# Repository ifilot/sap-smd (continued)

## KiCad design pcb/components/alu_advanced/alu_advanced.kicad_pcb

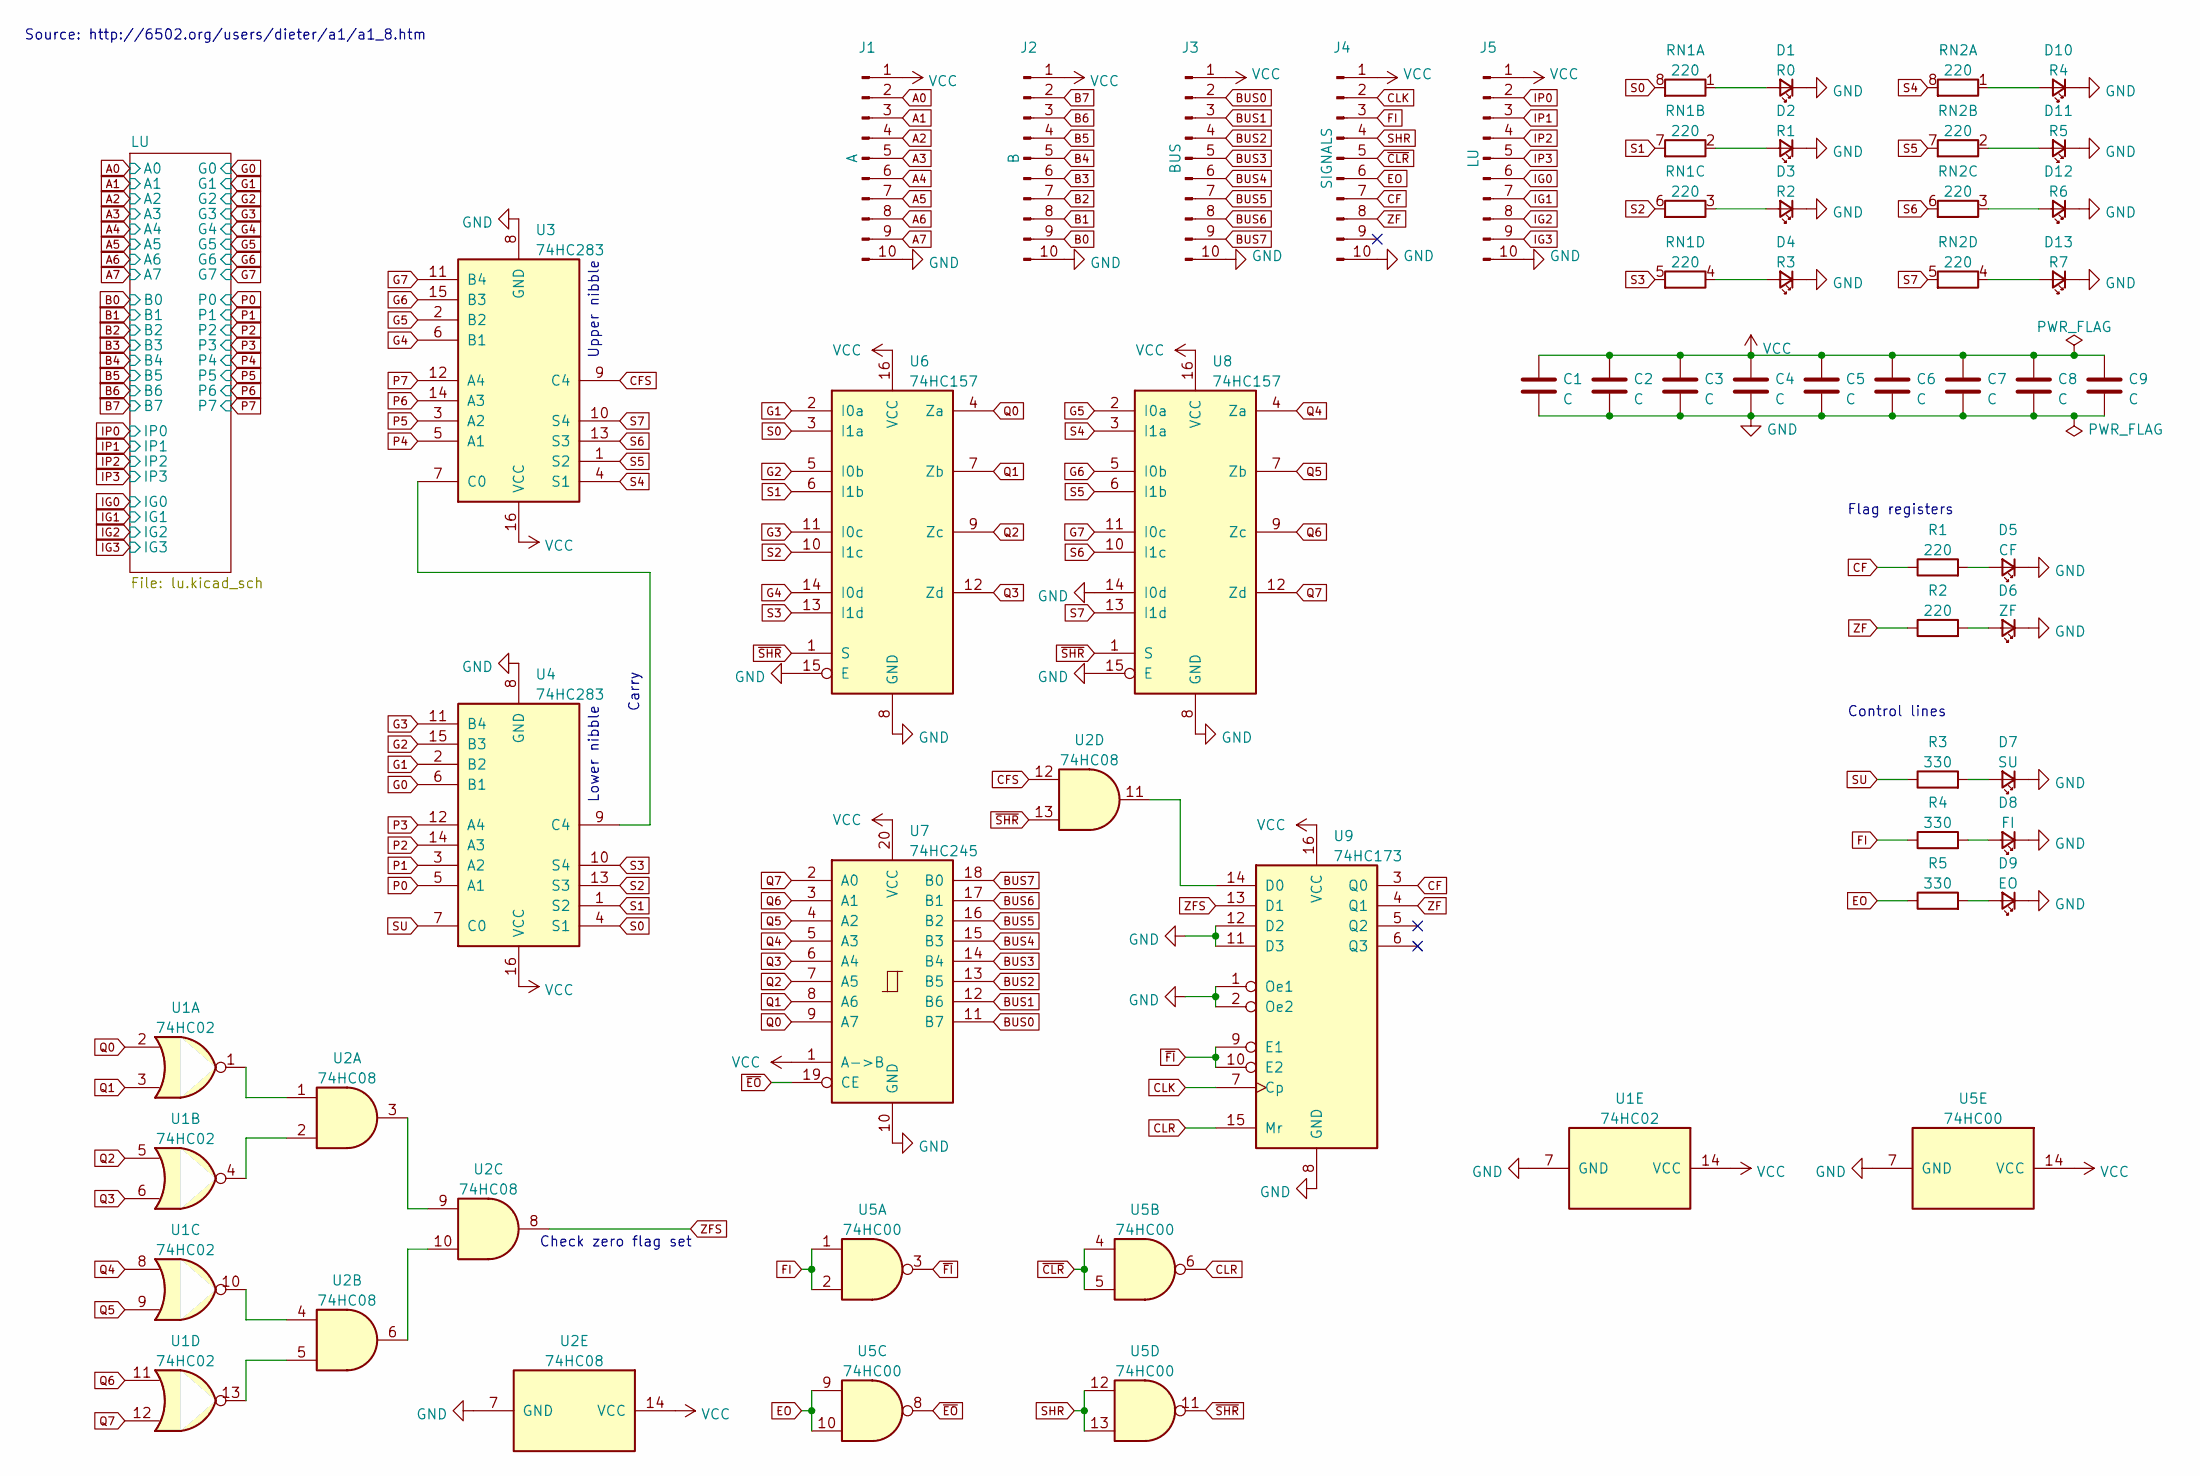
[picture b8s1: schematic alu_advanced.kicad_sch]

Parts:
C1, C2, C3, C4, C5, C6, C7, C8, C9: C; C_0805_2012Metric
D1: R0; LED_0805_2012Metric
D2: R1; LED_0805_2012Metric
D3: R2; LED_0805_2012Metric
D4: R3; LED_0805_2012Metric
D5: CF; LED_0805_2012Metric
D6: ZF; LED_0805_2012Metric
D7: SU; LED_0805_2012Metric
D8: FI; LED_0805_2012Metric
D9: EO; LED_0805_2012Metric
D10: R4; LED_0805_2012Metric
D11: R5; LED_0805_2012Metric
D12: R6; LED_0805_2012Metric
D13: R7; LED_0805_2012Metric
J1: A; PinHeader_1x10_P2.54mm_Vertical
J2: B; PinHeader_1x10_P2.54mm_Vertical
J3: BUS; PinHeader_1x10_P2.54mm_Vertical
J4: SIGNALS; PinHeader_1x10_P2.54mm_Vertical
J5: LU; PinHeader_1x10_P2.54mm_Vertical
R1, R2: 220; R_0805_2012Metric
R3, R4, R5: 330; R_0805_2012Metric
RN1, RN2: 220; R_Array_Convex_4x0603
U1: 74HC02; SO-14_3.9x8.65mm_P1.27mm
U2: 74HC08; SO-14_3.9x8.65mm_P1.27mm
U3, U4: 74HC283; SO-16_3.9x9.9mm_P1.27mm
U5: 74HC00; SO-14_3.9x8.65mm_P1.27mm
U6, U8: 74HC157; SO-16_3.9x9.9mm_P1.27mm
U7: 74HC245; SO-20_12.8x7.5mm_P1.27mm
U9: 74HC173; SO-16_3.9x9.9mm_P1.27mm

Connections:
A0: J1.2; also elsewhere on the board
A1: J1.3; also elsewhere on the board
A2: J1.4; also elsewhere on the board
A3: J1.5; also elsewhere on the board
A4: J1.6; also elsewhere on the board
A5: J1.7; also elsewhere on the board
A6: J1.8; also elsewhere on the board
A7: J1.9; also elsewhere on the board
B0: J2.9; also elsewhere on the board
B1: J2.8; also elsewhere on the board
B2: J2.7; also elsewhere on the board
B3: J2.6; also elsewhere on the board
B4: J2.5; also elsewhere on the board
B5: J2.4; also elsewhere on the board
B6: J2.3; also elsewhere on the board
B7: J2.2; also elsewhere on the board
BUS0: J3.2, U7.11 (B7)
BUS1: J3.3, U7.12 (B6)
BUS2: J3.4, U7.13 (B5)
BUS3: J3.5, U7.14 (B4)
BUS4: J3.6, U7.15 (B3)
BUS5: J3.7, U7.16 (B2)
BUS6: J3.8, U7.17 (B1)
BUS7: J3.9, U7.18 (B0)
CF: J4.7, R1.1, U9.3 (Q0)
CFS: U2.12, U3.9 (C4)
CLK: J4.2, U9.7 (Cp)
CLR: U5.6, U9.15 (Mr)
EO: J4.6, R5.1, U5.9, U5.10
FI: J4.3, R4.1, U5.1, U5.2
G0: U4.6 (B1); also elsewhere on the board
G1: U4.2 (B2), U6.2 (I0a); also elsewhere on the board
G2: U4.15 (B3), U6.5 (I0b); also elsewhere on the board
G3: U4.11 (B4), U6.11 (I0c); also elsewhere on the board
G4: U3.6 (B1), U6.14 (I0d); also elsewhere on the board
G5: U3.2 (B2), U8.2 (I0a); also elsewhere on the board
G6: U3.15 (B3), U8.5 (I0b); also elsewhere on the board
G7: U3.11 (B4), U8.11 (I0c); also elsewhere on the board
GND: C1.2, C2.2, C3.2, C4.2, C5.2, C6.2, C7.2, C8.2, C9.2, D1.1 (K), D2.1 (K), D3.1 (K), D4.1 (K), D5.1 (K), D6.1 (K), D7.1 (K), D8.1 (K), D9.1 (K), D10.1 (K), D11.1 (K), D12.1 (K), D13.1 (K), J1.10, J2.10, J3.10, J4.10, J5.10, U1.7 (GND), U2.7 (GND), U3.8 (GND), U4.8 (GND), U5.7 (GND), U6.8 (GND), U6.15 (E), U7.10 (GND), U8.8 (GND), U8.14 (I0d), U8.15 (E), U9.1 (Oe1), U9.2 (Oe2), U9.8 (GND), U9.11 (D3), U9.12 (D2); also elsewhere on the board
IG0: J5.6; also elsewhere on the board
IG1: J5.7; also elsewhere on the board
IG2: J5.8; also elsewhere on the board
IG3: J5.9; also elsewhere on the board
IP0: J5.2; also elsewhere on the board
IP1: J5.3; also elsewhere on the board
IP2: J5.4; also elsewhere on the board
IP3: J5.5; also elsewhere on the board
unnamed: D1.2 (A), RN1.1 (R1.1)
unnamed: D2.2 (A), RN1.2 (R2.1)
unnamed: D3.2 (A), RN1.3 (R3.1)
unnamed: D4.2 (A), RN1.4 (R4.1)
unnamed: D5.2 (A), R1.2
unnamed: D6.2 (A), R2.2
unnamed: D7.2 (A), R3.2
unnamed: D8.2 (A), R4.2
unnamed: D9.2 (A), R5.2
unnamed: D10.2 (A), RN2.1 (R1.1)
unnamed: D11.2 (A), RN2.2 (R2.1)
unnamed: D12.2 (A), RN2.3 (R3.1)
unnamed: D13.2 (A), RN2.4 (R4.1)
unnamed: U1.1, U2.1
unnamed: U1.4, U2.2
unnamed: U1.10, U2.4
unnamed: U1.13, U2.5
unnamed: U2.3, U2.9
unnamed: U2.6, U2.10
unnamed: U2.11, U9.14 (D0)
unnamed: U3.7 (C0), U4.9 (C4)
P0: U4.5 (A1); also elsewhere on the board
P1: U4.3 (A2); also elsewhere on the board
P2: U4.14 (A3); also elsewhere on the board
P3: U4.12 (A4); also elsewhere on the board
P4: U3.5 (A1); also elsewhere on the board
P5: U3.3 (A2); also elsewhere on the board
P6: U3.14 (A3); also elsewhere on the board
P7: U3.12 (A4); also elsewhere on the board
Q0: U1.2, U6.4 (Za), U7.9 (A7)
Q1: U1.3, U6.7 (Zb), U7.8 (A6)
Q2: U1.5, U6.9 (Zc), U7.7 (A5)
Q3: U1.6, U6.12 (Zd), U7.6 (A4)
Q4: U1.8, U7.5 (A3), U8.4 (Za)
Q5: U1.9, U7.4 (A2), U8.7 (Zb)
Q6: U1.11, U7.3 (A1), U8.9 (Zc)
Q7: U1.12, U7.2 (A0), U8.12 (Zd)
S0: RN1.8 (R1.2), U4.4 (S1), U6.3 (I1a)
S1: RN1.7 (R2.2), U4.1 (S2), U6.6 (I1b)
S2: RN1.6 (R3.2), U4.13 (S3), U6.10 (I1c)
S3: RN1.5 (R4.2), U4.10 (S4), U6.13 (I1d)
S4: RN2.8 (R1.2), U3.4 (S1), U8.3 (I1a)
S5: RN2.7 (R2.2), U3.1 (S2), U8.6 (I1b)
S6: RN2.6 (R3.2), U3.13 (S3), U8.10 (I1c)
S7: RN2.5 (R4.2), U3.10 (S4), U8.13 (I1d)
SHR: J4.4, U5.12, U5.13
SU: R3.1, U4.7 (C0)
VCC: C1.1, C2.1, C3.1, C4.1, C5.1, C6.1, C7.1, C8.1, C9.1, J1.1, J2.1, J3.1, J4.1, J5.1, U1.14 (VCC), U2.14 (VCC), U3.16 (VCC), U4.16 (VCC), U5.14 (VCC), U6.16 (VCC), U7.1 (A->B), U7.20 (VCC), U8.16 (VCC), U9.16 (VCC); also elsewhere on the board
ZF: J4.8, R2.1, U9.4 (Q1)
ZFS: U2.8, U9.13 (D1)
~CLR: J4.5, U5.4, U5.5
~EO: U5.8, U7.19 (CE)
~FI: U5.3, U9.9 (E1), U9.10 (E2)
~SHR: U2.13, U5.11, U6.1 (S), U8.1 (S)

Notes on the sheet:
Control lines
Flag registers
Upper nibble
Check zero flag set
Source: http://6502.org/users/dieter/a1/a1_8.htm
Carry
Lower nibble

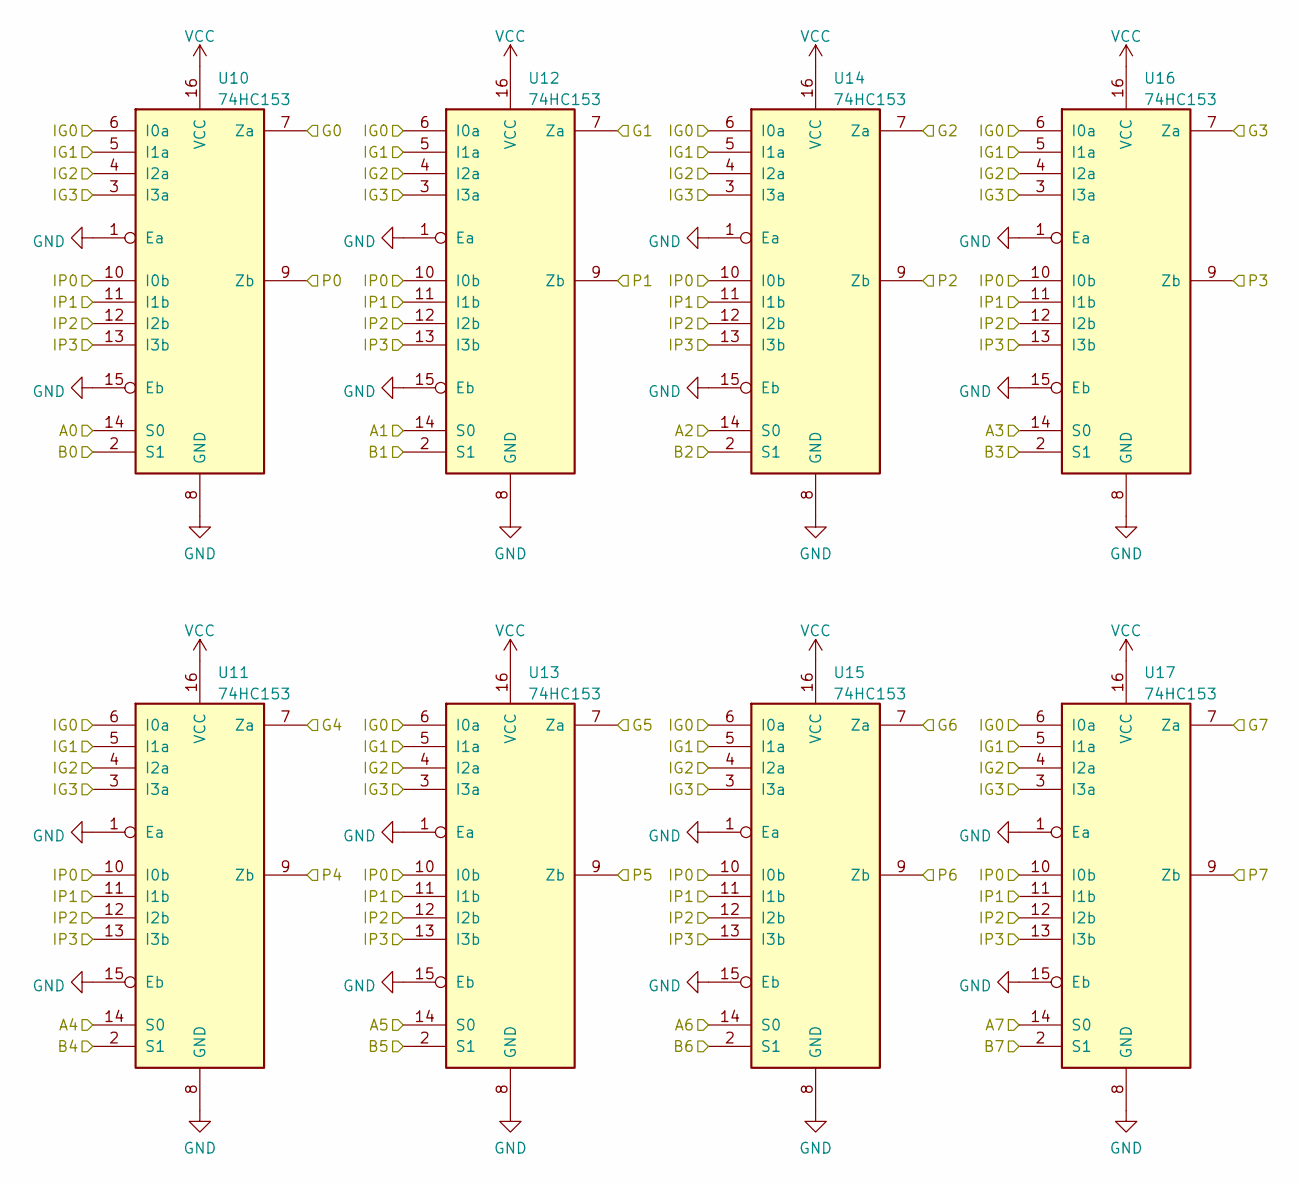
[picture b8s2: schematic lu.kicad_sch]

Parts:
U10, U11, U12, U13, U14, U15, U16, U17: 74HC153; SO-16_3.9x9.9mm_P1.27mm

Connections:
A0: U10.14 (S0); also elsewhere on the board
A1: U12.14 (S0); also elsewhere on the board
A2: U14.14 (S0); also elsewhere on the board
A3: U16.14 (S0); also elsewhere on the board
A4: U11.14 (S0); also elsewhere on the board
A5: U13.14 (S0); also elsewhere on the board
A6: U15.14 (S0); also elsewhere on the board
A7: U17.14 (S0); also elsewhere on the board
B0: U10.2 (S1); also elsewhere on the board
B1: U12.2 (S1); also elsewhere on the board
B2: U14.2 (S1); also elsewhere on the board
B3: U16.2 (S1); also elsewhere on the board
B4: U11.2 (S1); also elsewhere on the board
B5: U13.2 (S1); also elsewhere on the board
B6: U15.2 (S1); also elsewhere on the board
B7: U17.2 (S1); also elsewhere on the board
G0: U10.7 (Za); also elsewhere on the board
G1: U12.7 (Za); also elsewhere on the board
G2: U14.7 (Za); also elsewhere on the board
G3: U16.7 (Za); also elsewhere on the board
G4: U11.7 (Za); also elsewhere on the board
G5: U13.7 (Za); also elsewhere on the board
G6: U15.7 (Za); also elsewhere on the board
G7: U17.7 (Za); also elsewhere on the board
GND: U10.1 (Ea), U10.8 (GND), U10.15 (Eb), U11.1 (Ea), U11.8 (GND), U11.15 (Eb), U12.1 (Ea), U12.8 (GND), U12.15 (Eb), U13.1 (Ea), U13.8 (GND), U13.15 (Eb), U14.1 (Ea), U14.8 (GND), U14.15 (Eb), U15.1 (Ea), U15.8 (GND), U15.15 (Eb), U16.1 (Ea), U16.8 (GND), U16.15 (Eb), U17.1 (Ea), U17.8 (GND), U17.15 (Eb); also elsewhere on the board
IG0: U10.6 (I0a), U11.6 (I0a), U12.6 (I0a), U13.6 (I0a), U14.6 (I0a), U15.6 (I0a), U16.6 (I0a), U17.6 (I0a); also elsewhere on the board
IG1: U10.5 (I1a), U11.5 (I1a), U12.5 (I1a), U13.5 (I1a), U14.5 (I1a), U15.5 (I1a), U16.5 (I1a), U17.5 (I1a); also elsewhere on the board
IG2: U10.4 (I2a), U11.4 (I2a), U12.4 (I2a), U13.4 (I2a), U14.4 (I2a), U15.4 (I2a), U16.4 (I2a), U17.4 (I2a); also elsewhere on the board
IG3: U10.3 (I3a), U11.3 (I3a), U12.3 (I3a), U13.3 (I3a), U14.3 (I3a), U15.3 (I3a), U16.3 (I3a), U17.3 (I3a); also elsewhere on the board
IP0: U10.10 (I0b), U11.10 (I0b), U12.10 (I0b), U13.10 (I0b), U14.10 (I0b), U15.10 (I0b), U16.10 (I0b), U17.10 (I0b); also elsewhere on the board
IP1: U10.11 (I1b), U11.11 (I1b), U12.11 (I1b), U13.11 (I1b), U14.11 (I1b), U15.11 (I1b), U16.11 (I1b), U17.11 (I1b); also elsewhere on the board
IP2: U10.12 (I2b), U11.12 (I2b), U12.12 (I2b), U13.12 (I2b), U14.12 (I2b), U15.12 (I2b), U16.12 (I2b), U17.12 (I2b); also elsewhere on the board
IP3: U10.13 (I3b), U11.13 (I3b), U12.13 (I3b), U13.13 (I3b), U14.13 (I3b), U15.13 (I3b), U16.13 (I3b), U17.13 (I3b); also elsewhere on the board
P0: U10.9 (Zb); also elsewhere on the board
P1: U12.9 (Zb); also elsewhere on the board
P2: U14.9 (Zb); also elsewhere on the board
P3: U16.9 (Zb); also elsewhere on the board
P4: U11.9 (Zb); also elsewhere on the board
P5: U13.9 (Zb); also elsewhere on the board
P6: U15.9 (Zb); also elsewhere on the board
P7: U17.9 (Zb); also elsewhere on the board
VCC: U10.16 (VCC), U11.16 (VCC), U12.16 (VCC), U13.16 (VCC), U14.16 (VCC), U15.16 (VCC), U16.16 (VCC), U17.16 (VCC); also elsewhere on the board

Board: 2 copper layers, 51 parts (5 on the bottom side), 101 nets, no tracks yet.

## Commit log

2025-01-14 Adding CERN license
2025-01-14 Adding license file
2025-01-14 Showing demo
2025-01-15 Polishing Arduino Leonardo script to test LCD Display
2025-01-16 Modifying README.md and initial commit docs
2025-01-16 deploy: 651839604ced14f607ccee0d7958162028918309
2025-01-16 Adding logo design file
2025-01-17 Initial commit instruction decoder to documentation
2025-01-17 deploy: 7e05e96c52622dcd8672e2f93eff8e06e995d482
2025-01-19 Expanding documentation
2025-01-19 deploy: 3a388593254523a892c930b86c1c971830fbae64
2025-01-26 Adding t-state explanation
2025-01-26 deploy: c7d25511b9d4da231f3ea45f070992f05c98a8c0
